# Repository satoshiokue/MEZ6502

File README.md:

# MEZ6502
W65C816S/W65C02S/6502 Mezzanine board for EMUZ80  

R1 >= 2k LEDの明るさで選んでください  
R2 = 3.3k  
C1 = 0.1uF  

https://github.com/satoshiokue/EMUZ80-6502

MEZ6502専用プリント基板 - オレンジピコショップ  
https://store.shopping.yahoo.co.jp/orangepicoshop/pico-a-058.html

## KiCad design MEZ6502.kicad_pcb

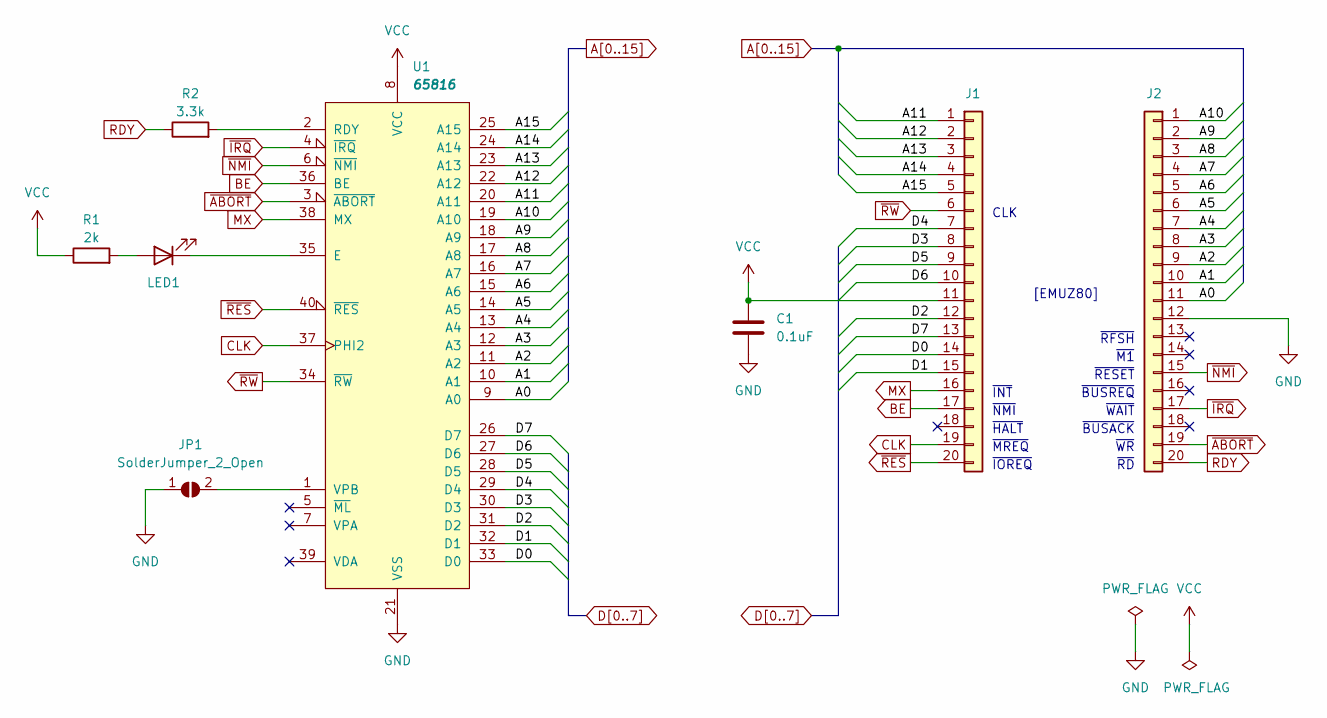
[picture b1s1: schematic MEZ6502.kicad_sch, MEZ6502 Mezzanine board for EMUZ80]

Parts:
C1: 0.1uF; C_Disc_D3.8mm_W2.6mm_P2.50mm
J1, J2: Conn_01x20; PinHeader_1x20_P2.54mm_Vertical
JP1: SolderJumper_2_Open; SolderJumper-2_P1.3mm_Open_Pad1.0x1.5mm
LED1: LED; LED_D3.0mm
R1: 2k; R_Axial_DIN0207_L6.3mm_D2.5mm_P10.16mm_Horizontal
R2: 3.3k; R_Axial_DIN0207_L6.3mm_D2.5mm_P10.16mm_Horizontal
U1: 65816; DIP-40_W15.24mm

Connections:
A0: J2.11, U1.9 (A0)
A1: J2.10, U1.10 (A1)
A2: J2.9, U1.11 (A2)
A3: J2.8, U1.12 (A3)
A4: J2.7, U1.13 (A4)
A5: J2.6, U1.14 (A5)
A6: J2.5, U1.15 (A6)
A7: J2.4, U1.16 (A7)
A8: J2.3, U1.17 (A8)
A9: J2.2, U1.18 (A9)
A10: J2.1, U1.19 (A10)
A11: J1.1, U1.20 (A11)
A12: J1.2, U1.22 (A12)
A13: J1.3, U1.23 (A13)
A14: J1.4, U1.24 (A14)
A15: J1.5, U1.25 (A15)
BE: J1.17, U1.36 (BE)
CLK: J1.19, U1.37 (PHI2)
D0: J1.14, U1.33 (D0)
D1: J1.15, U1.32 (D1)
D2: J1.12, U1.31 (D2)
D3: J1.8, U1.30 (D3)
D4: J1.7, U1.29 (D4)
D5: J1.9, U1.28 (D5)
D6: J1.10, U1.27 (D6)
D7: J1.13, U1.26 (D7)
GND: C1.2, J2.12, JP1.1 (A), U1.21 (VSS)
MX: J1.16, U1.38 (MX)
unnamed: LED1.1 (K), U1.35 (E)
unnamed: LED1.2 (A), R1.2
unnamed: R2.2, U1.2 (RDY)
unnamed: JP1.2 (B), U1.1 (VPB)
RDY: J2.20, R2.1
VCC: C1.1, J1.11, R1.1, U1.8 (VCC)
~ABORT: J2.19, U1.3 (~ABORT)
~IRQ: J2.17, U1.4 (~IRQ)
~NMI: J2.15, U1.6 (~NMI)
~RES: J1.20, U1.40 (~RES)
~RW: J1.6, U1.34 (~RW)

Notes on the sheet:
~{RFSH}
[EMUZ80]
~{NMI}
CLK
~{M1}
~{INT}
~{BUSREQ}
~{WAIT}
~{IOREQ}
~{BUSACK}
~{WR}
~{MREQ}
~{RESET}
~{HALT}
~{RD}

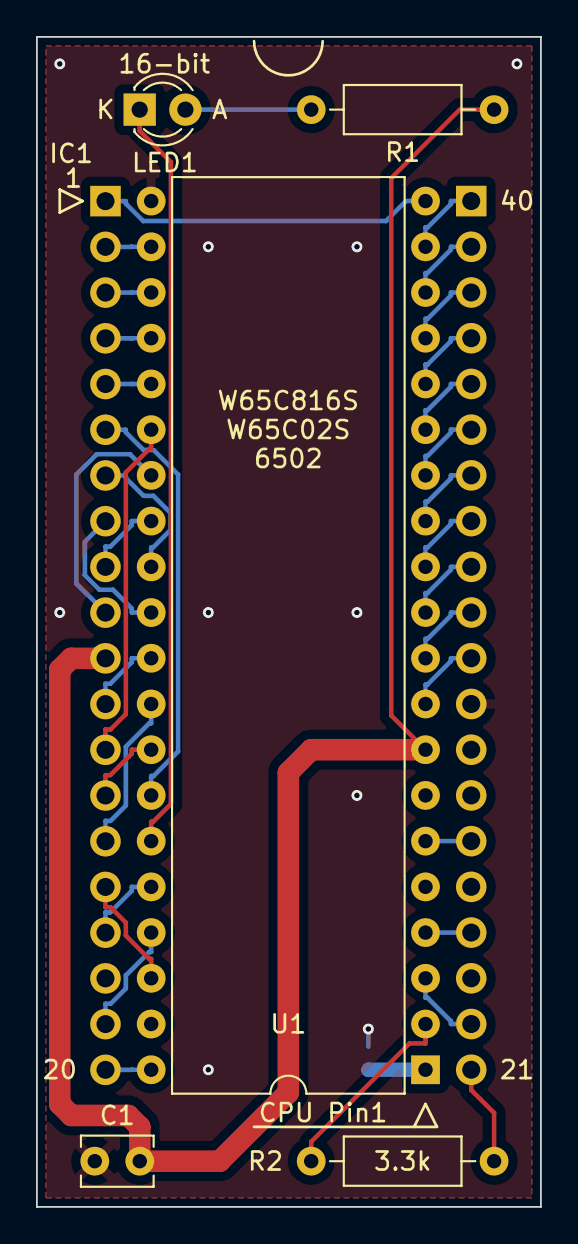
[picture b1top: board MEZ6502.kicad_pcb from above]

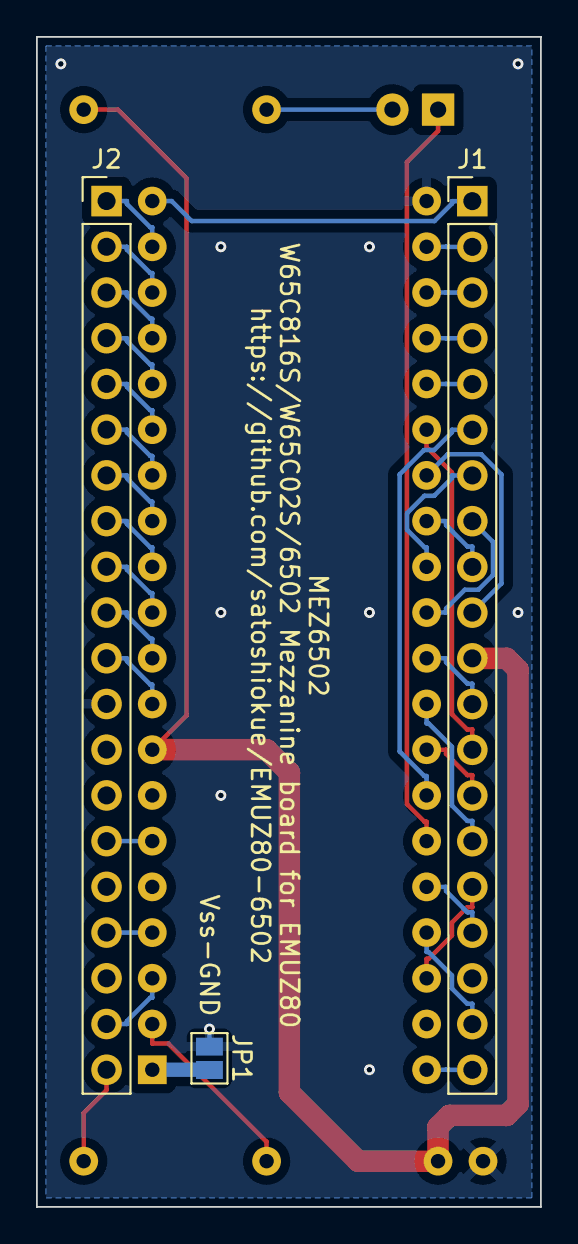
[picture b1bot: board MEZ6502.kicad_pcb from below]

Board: 2 copper layers, 28.0 x 65.0 mm, 8 parts (3 on the bottom side), 39 nets.

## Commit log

2022-09-03 Create foo
